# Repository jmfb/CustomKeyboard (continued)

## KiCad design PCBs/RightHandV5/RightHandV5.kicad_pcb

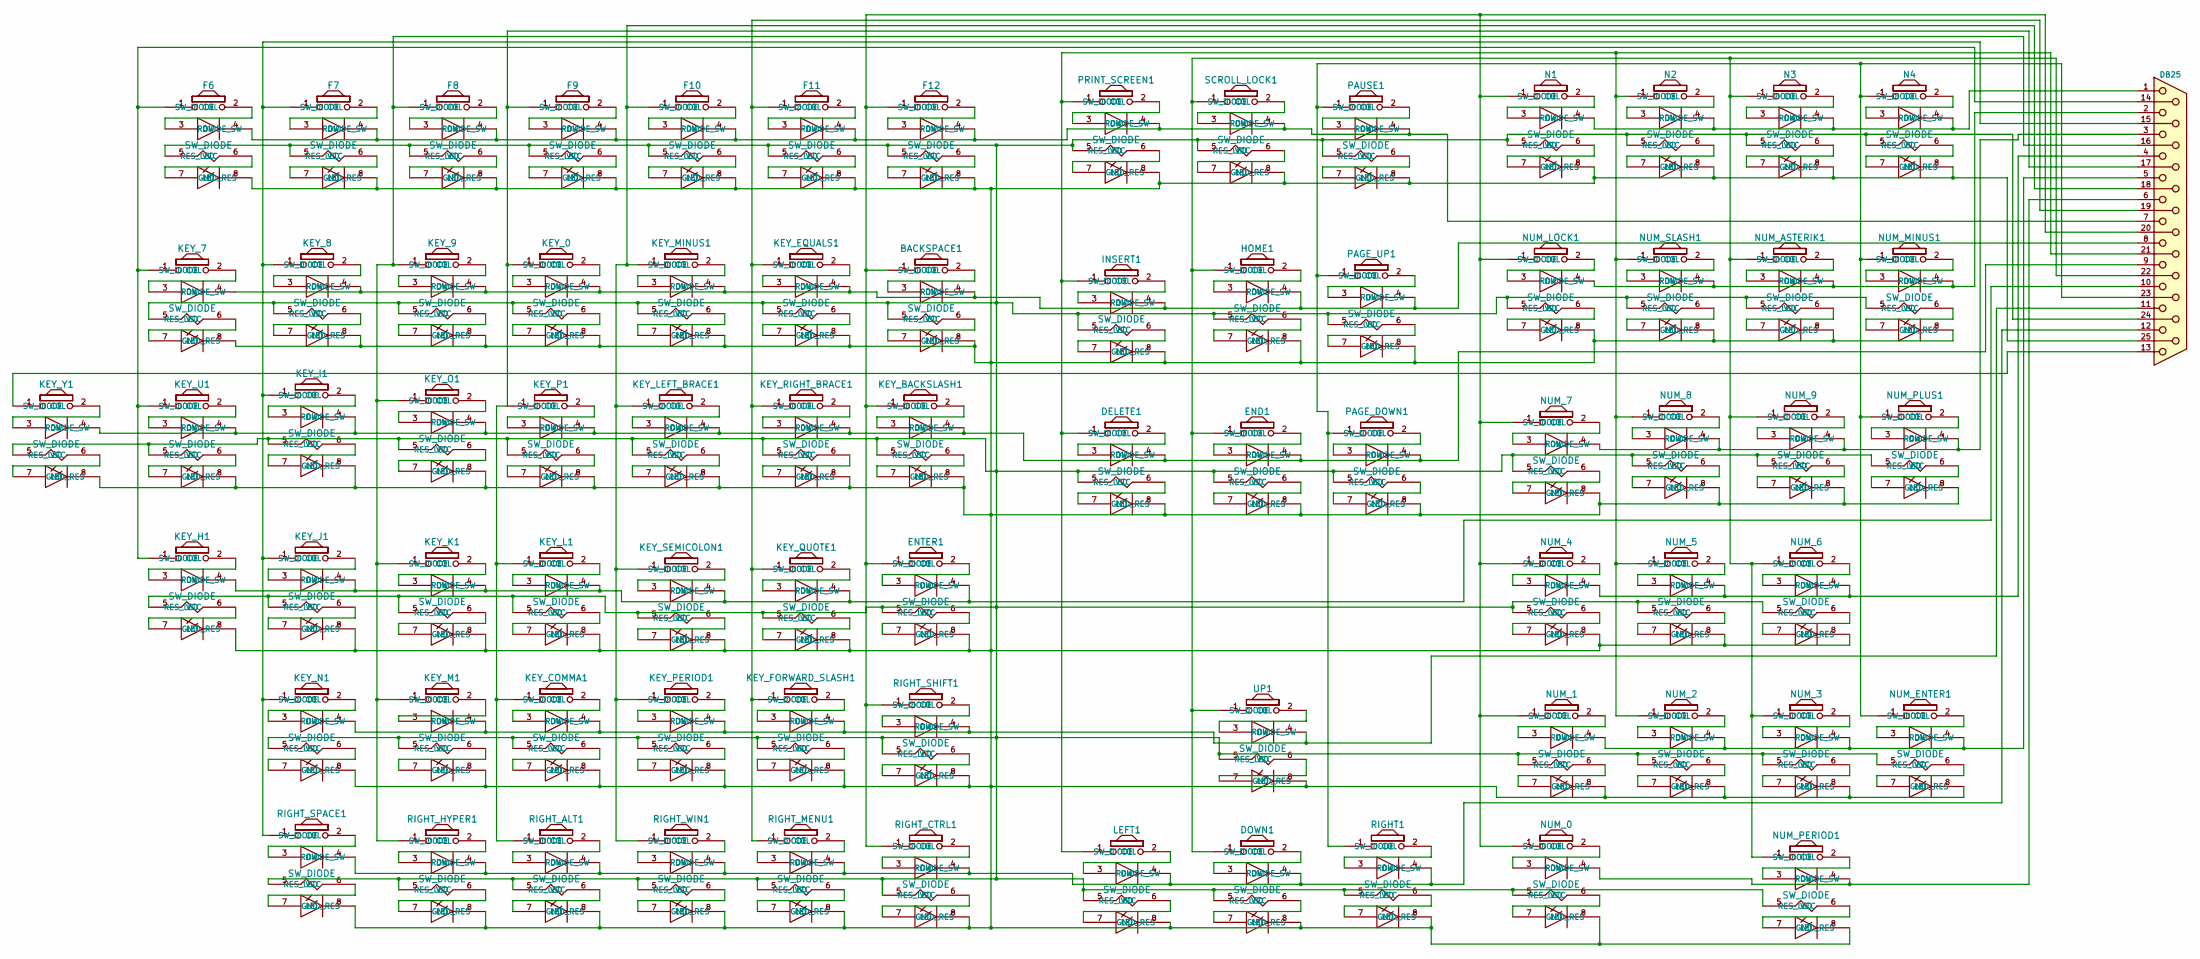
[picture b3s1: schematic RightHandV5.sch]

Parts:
BACKSPACE1: SW_DIODE; SW2_DIODE_R
DB25: DB25_Female; DB25FD
DELETE1: SW_DIODE
DOWN1: SW_DIODE
END1: SW_DIODE
ENTER1: SW_DIODE; SW2_DIODE_R
F6, F7, F8, F9, F10, F11, F12: SW_DIODE
HOME1: SW_DIODE
INSERT1: SW_DIODE
KEY_0, KEY_7, KEY_8, KEY_9: SW_DIODE
KEY_BACKSLASH1: SW_DIODE; SW_DIODE_RSIDE
KEY_COMMA1: SW_DIODE
KEY_EQUALS1: SW_DIODE
KEY_FORWARD_SLASH1: SW_DIODE
KEY_H1: SW_DIODE
KEY_I1: SW_DIODE
KEY_J1: SW_DIODE
KEY_K1: SW_DIODE
KEY_L1: SW_DIODE
KEY_LEFT_BRACE1: SW_DIODE
KEY_M1: SW_DIODE
KEY_MINUS1: SW_DIODE
KEY_N1: SW_DIODE
KEY_O1: SW_DIODE
KEY_P1: SW_DIODE
KEY_PERIOD1: SW_DIODE
KEY_QUOTE1: SW_DIODE
KEY_RIGHT_BRACE1: SW_DIODE; SW_DIODE_RTOP
KEY_SEMICOLON1: SW_DIODE
KEY_U1: SW_DIODE
KEY_Y1: SW_DIODE
LEFT1: SW_DIODE
N1, N2, N3, N4: SW_DIODE
NUM_0: SW_DIODE; SW2_DIODE_L
NUM_1, NUM_2, NUM_3, NUM_4, NUM_5, NUM_6, NUM_7, NUM_8, NUM_9: SW_DIODE
NUM_ASTERIK1: SW_DIODE
NUM_ENTER1: SW_DIODE; SW2_DIODE_L_RSIDE
NUM_LOCK1: SW_DIODE
NUM_MINUS1: SW_DIODE
NUM_PERIOD1: SW_DIODE
NUM_PLUS1: SW_DIODE; SW2_DIODE_L_RSIDE
NUM_SLASH1: SW_DIODE
PAGE_DOWN1: SW_DIODE
PAGE_UP1: SW_DIODE
PAUSE1: SW_DIODE
PRINT_SCREEN1: SW_DIODE
RIGHT1: SW_DIODE
RIGHT_ALT1: SW_DIODE
RIGHT_CTRL1: SW_DIODE; SW_DIODE_RTOP
RIGHT_HYPER1: SW_DIODE
RIGHT_MENU1: SW_DIODE; SW_DIODE_RTOP
RIGHT_SHIFT1: SW_DIODE; SW2_DIODE_R_RSIDE
RIGHT_SPACE1: SW_DIODE; SW2_DIODE_R_RSIDE
RIGHT_WIN1: SW_DIODE
SCROLL_LOCK1: SW_DIODE
UP1: SW_DIODE

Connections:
unnamed: BACKSPACE1.1 (COL), DB25.20, ENTER1.1 (COL), F12.1 (COL), KEY_BACKSLASH1.1 (COL), N1.1 (COL), NUM_0.1 (COL), NUM_1.1 (COL), NUM_4.1 (COL), NUM_7.1 (COL), NUM_LOCK1.1 (COL), RIGHT_CTRL1.1 (COL), RIGHT_SHIFT1.1 (COL)
unnamed: BACKSPACE1.2 (SW_DIODE), BACKSPACE1.3 (DIODE_SW)
unnamed: BACKSPACE1.4 (ROW), DB25.8, HOME1.4 (ROW), INSERT1.4 (ROW), KEY_0.4 (ROW), KEY_7.4 (ROW), KEY_8.4 (ROW), KEY_9.4 (ROW), KEY_EQUALS1.4 (ROW), KEY_MINUS1.4 (ROW), PAGE_UP1.4 (ROW)
unnamed: BACKSPACE1.5 (VCC), DB25.24, DELETE1.5 (VCC), DOWN1.5 (VCC), END1.5 (VCC), ENTER1.5 (VCC), F6.5 (VCC), F7.5 (VCC), F8.5 (VCC), F9.5 (VCC), F10.5 (VCC), F11.5 (VCC), F12.5 (VCC), HOME1.5 (VCC), INSERT1.5 (VCC), KEY_0.5 (VCC), KEY_7.5 (VCC), KEY_8.5 (VCC), KEY_9.5 (VCC), KEY_BACKSLASH1.5 (VCC), KEY_COMMA1.5 (VCC), KEY_EQUALS1.5 (VCC), KEY_FORWARD_SLASH1.5 (VCC), KEY_H1.5 (VCC), KEY_I1.5 (VCC), KEY_J1.5 (VCC), KEY_K1.5 (VCC), KEY_L1.5 (VCC), KEY_LEFT_BRACE1.5 (VCC), KEY_M1.5 (VCC), KEY_MINUS1.5 (VCC), KEY_N1.5 (VCC), KEY_O1.5 (VCC), KEY_P1.5 (VCC), KEY_PERIOD1.5 (VCC), KEY_QUOTE1.5 (VCC), KEY_RIGHT_BRACE1.5 (VCC), KEY_SEMICOLON1.5 (VCC), KEY_U1.5 (VCC), KEY_Y1.5 (VCC), LEFT1.5 (VCC), N1.5 (VCC), N2.5 (VCC), N3.5 (VCC), N4.5 (VCC), NUM_0.5 (VCC), NUM_1.5 (VCC), NUM_2.5 (VCC), NUM_3.5 (VCC), NUM_4.5 (VCC), NUM_5.5 (VCC), NUM_6.5 (VCC), NUM_7.5 (VCC), NUM_8.5 (VCC), NUM_9.5 (VCC), NUM_ASTERIK1.5 (VCC), NUM_ENTER1.5 (VCC), NUM_LOCK1.5 (VCC), NUM_MINUS1.5 (VCC), NUM_PERIOD1.5 (VCC), NUM_PLUS1.5 (VCC), NUM_SLASH1.5 (VCC), PAGE_DOWN1.5 (VCC), PAGE_UP1.5 (VCC), PAUSE1.5 (VCC), PRINT_SCREEN1.5 (VCC), RIGHT1.5 (VCC), RIGHT_ALT1.5 (VCC), RIGHT_CTRL1.5 (VCC), RIGHT_HYPER1.5 (VCC), RIGHT_MENU1.5 (VCC), RIGHT_SHIFT1.5 (VCC), RIGHT_SPACE1.5 (VCC), RIGHT_WIN1.5 (VCC), SCROLL_LOCK1.5 (VCC), UP1.5 (VCC)
unnamed: BACKSPACE1.6 (RES_LED), BACKSPACE1.7 (LED_RES)
unnamed: BACKSPACE1.8 (GND), DB25.25, DELETE1.8 (GND), DOWN1.8 (GND), END1.8 (GND), ENTER1.8 (GND), F6.8 (GND), F7.8 (GND), F8.8 (GND), F9.8 (GND), F10.8 (GND), F11.8 (GND), F12.8 (GND), HOME1.8 (GND), INSERT1.8 (GND), KEY_0.8 (GND), KEY_7.8 (GND), KEY_8.8 (GND), KEY_9.8 (GND), KEY_BACKSLASH1.8 (GND), KEY_COMMA1.8 (GND), KEY_EQUALS1.8 (GND), KEY_FORWARD_SLASH1.8 (GND), KEY_H1.8 (GND), KEY_I1.8 (GND), KEY_J1.8 (GND), KEY_K1.8 (GND), KEY_L1.8 (GND), KEY_LEFT_BRACE1.8 (GND), KEY_M1.8 (GND), KEY_MINUS1.8 (GND), KEY_N1.8 (GND), KEY_O1.8 (GND), KEY_P1.8 (GND), KEY_PERIOD1.8 (GND), KEY_QUOTE1.8 (GND), KEY_RIGHT_BRACE1.8 (GND), KEY_SEMICOLON1.8 (GND), KEY_U1.8 (GND), KEY_Y1.8 (GND), LEFT1.8 (GND), N1.8 (GND), N2.8 (GND), N3.8 (GND), N4.8 (GND), NUM_0.8 (GND), NUM_1.8 (GND), NUM_2.8 (GND), NUM_3.8 (GND), NUM_4.8 (GND), NUM_5.8 (GND), NUM_6.8 (GND), NUM_7.8 (GND), NUM_8.8 (GND), NUM_9.8 (GND), NUM_ASTERIK1.8 (GND), NUM_ENTER1.8 (GND), NUM_LOCK1.8 (GND), NUM_MINUS1.8 (GND), NUM_PERIOD1.8 (GND), NUM_PLUS1.8 (GND), NUM_SLASH1.8 (GND), PAGE_DOWN1.8 (GND), PAGE_UP1.8 (GND), PAUSE1.8 (GND), PRINT_SCREEN1.8 (GND), RIGHT1.8 (GND), RIGHT_ALT1.8 (GND), RIGHT_CTRL1.8 (GND), RIGHT_HYPER1.8 (GND), RIGHT_MENU1.8 (GND), RIGHT_SHIFT1.8 (GND), RIGHT_SPACE1.8 (GND), RIGHT_WIN1.8 (GND), SCROLL_LOCK1.8 (GND), UP1.8 (GND)
unnamed: DB25.1, N1.4 (ROW), N2.4 (ROW), N3.4 (ROW), N4.4 (ROW)
unnamed: DB25.2, NUM_ASTERIK1.4 (ROW), NUM_LOCK1.4 (ROW), NUM_MINUS1.4 (ROW), NUM_SLASH1.4 (ROW)
unnamed: DB25.3, NUM_7.4 (ROW), NUM_8.4 (ROW), NUM_9.4 (ROW), NUM_PLUS1.4 (ROW)
unnamed: DB25.4, NUM_4.4 (ROW), NUM_5.4 (ROW), NUM_6.4 (ROW)
unnamed: DB25.5, NUM_1.4 (ROW), NUM_2.4 (ROW), NUM_3.4 (ROW), NUM_ENTER1.4 (ROW)
unnamed: DB25.6, NUM_0.4 (ROW), NUM_PERIOD1.4 (ROW)
unnamed: DB25.7, F6.4 (ROW), F7.4 (ROW), F8.4 (ROW), F9.4 (ROW), F10.4 (ROW), F11.4 (ROW), F12.4 (ROW), PAUSE1.4 (ROW), PRINT_SCREEN1.4 (ROW), SCROLL_LOCK1.4 (ROW)
unnamed: DB25.9, DELETE1.4 (ROW), END1.4 (ROW), KEY_BACKSLASH1.4 (ROW), KEY_I1.4 (ROW), KEY_LEFT_BRACE1.4 (ROW), KEY_O1.4 (ROW), KEY_P1.4 (ROW), KEY_RIGHT_BRACE1.4 (ROW), KEY_U1.4 (ROW), KEY_Y1.4 (ROW), PAGE_DOWN1.4 (ROW)
unnamed: DB25.10, ENTER1.4 (ROW), KEY_H1.4 (ROW), KEY_J1.4 (ROW), KEY_K1.4 (ROW), KEY_L1.4 (ROW), KEY_QUOTE1.4 (ROW), KEY_SEMICOLON1.4 (ROW)
unnamed: DB25.11, KEY_COMMA1.4 (ROW), KEY_FORWARD_SLASH1.4 (ROW), KEY_M1.4 (ROW), KEY_N1.4 (ROW), KEY_PERIOD1.4 (ROW), RIGHT_SHIFT1.4 (ROW), UP1.4 (ROW)
unnamed: DB25.12, DOWN1.4 (ROW), LEFT1.4 (ROW), RIGHT1.4 (ROW), RIGHT_ALT1.4 (ROW), RIGHT_CTRL1.4 (ROW), RIGHT_HYPER1.4 (ROW), RIGHT_MENU1.4 (ROW), RIGHT_SPACE1.4 (ROW), RIGHT_WIN1.4 (ROW)
unnamed: DB25.13, KEY_Y1.1 (COL)
unnamed: DB25.14, F6.1 (COL), KEY_7.1 (COL), KEY_H1.1 (COL), KEY_U1.1 (COL)
unnamed: DB25.15, F7.1 (COL), KEY_8.1 (COL), KEY_I1.1 (COL), KEY_J1.1 (COL), KEY_N1.1 (COL), RIGHT_SPACE1.1 (COL)
unnamed: DB25.16, F8.1 (COL), KEY_9.1 (COL), KEY_K1.1 (COL), KEY_M1.1 (COL), KEY_O1.1 (COL), RIGHT_HYPER1.1 (COL)
unnamed: DB25.17, F9.1 (COL), KEY_0.1 (COL), KEY_COMMA1.1 (COL), KEY_L1.1 (COL), KEY_P1.1 (COL), RIGHT_ALT1.1 (COL)
unnamed: DB25.18, F10.1 (COL), KEY_LEFT_BRACE1.1 (COL), KEY_MINUS1.1 (COL), KEY_PERIOD1.1 (COL), KEY_SEMICOLON1.1 (COL), RIGHT_WIN1.1 (COL)
unnamed: DB25.19, F11.1 (COL), KEY_EQUALS1.1 (COL), KEY_FORWARD_SLASH1.1 (COL), KEY_QUOTE1.1 (COL), KEY_RIGHT_BRACE1.1 (COL), RIGHT_MENU1.1 (COL)
unnamed: DB25.21, DELETE1.1 (COL), INSERT1.1 (COL), LEFT1.1 (COL), N2.1 (COL), NUM_2.1 (COL), NUM_5.1 (COL), NUM_8.1 (COL), NUM_SLASH1.1 (COL), PRINT_SCREEN1.1 (COL)
unnamed: DB25.22, DOWN1.1 (COL), END1.1 (COL), HOME1.1 (COL), N3.1 (COL), NUM_3.1 (COL), NUM_6.1 (COL), NUM_9.1 (COL), NUM_ASTERIK1.1 (COL), NUM_PERIOD1.1 (COL), SCROLL_LOCK1.1 (COL), UP1.1 (COL)
unnamed: DB25.23, N4.1 (COL), NUM_ENTER1.1 (COL), NUM_MINUS1.1 (COL), NUM_PLUS1.1 (COL), PAGE_DOWN1.1 (COL), PAGE_UP1.1 (COL), PAUSE1.1 (COL), RIGHT1.1 (COL)
unnamed: DELETE1.2 (SW_DIODE), DELETE1.3 (DIODE_SW)
unnamed: DELETE1.6 (RES_LED), DELETE1.7 (LED_RES)
unnamed: DOWN1.2 (SW_DIODE), DOWN1.3 (DIODE_SW)
unnamed: DOWN1.6 (RES_LED), DOWN1.7 (LED_RES)
unnamed: END1.2 (SW_DIODE), END1.3 (DIODE_SW)
unnamed: END1.6 (RES_LED), END1.7 (LED_RES)
unnamed: ENTER1.2 (SW_DIODE), ENTER1.3 (DIODE_SW)
unnamed: ENTER1.6 (RES_LED), ENTER1.7 (LED_RES)
unnamed: F6.2 (SW_DIODE), F6.3 (DIODE_SW)
unnamed: F6.6 (RES_LED), F6.7 (LED_RES)
unnamed: F7.2 (SW_DIODE), F7.3 (DIODE_SW)
unnamed: F7.6 (RES_LED), F7.7 (LED_RES)
unnamed: F8.2 (SW_DIODE), F8.3 (DIODE_SW)
unnamed: F8.6 (RES_LED), F8.7 (LED_RES)
unnamed: F9.2 (SW_DIODE), F9.3 (DIODE_SW)
unnamed: F9.6 (RES_LED), F9.7 (LED_RES)
unnamed: F10.2 (SW_DIODE), F10.3 (DIODE_SW)
unnamed: F10.6 (RES_LED), F10.7 (LED_RES)
unnamed: F11.2 (SW_DIODE), F11.3 (DIODE_SW)
unnamed: F11.6 (RES_LED), F11.7 (LED_RES)
unnamed: F12.2 (SW_DIODE), F12.3 (DIODE_SW)
unnamed: F12.6 (RES_LED), F12.7 (LED_RES)
unnamed: HOME1.2 (SW_DIODE), HOME1.3 (DIODE_SW)
unnamed: HOME1.6 (RES_LED), HOME1.7 (LED_RES)
unnamed: INSERT1.2 (SW_DIODE), INSERT1.3 (DIODE_SW)
unnamed: INSERT1.6 (RES_LED), INSERT1.7 (LED_RES)
unnamed: KEY_0.2 (SW_DIODE), KEY_0.3 (DIODE_SW)
unnamed: KEY_0.6 (RES_LED), KEY_0.7 (LED_RES)
unnamed: KEY_7.2 (SW_DIODE), KEY_7.3 (DIODE_SW)
unnamed: KEY_7.6 (RES_LED), KEY_7.7 (LED_RES)
unnamed: KEY_8.2 (SW_DIODE), KEY_8.3 (DIODE_SW)
unnamed: KEY_8.6 (RES_LED), KEY_8.7 (LED_RES)
unnamed: KEY_9.2 (SW_DIODE), KEY_9.3 (DIODE_SW)
unnamed: KEY_9.6 (RES_LED), KEY_9.7 (LED_RES)
unnamed: KEY_BACKSLASH1.2 (SW_DIODE), KEY_BACKSLASH1.3 (DIODE_SW)
unnamed: KEY_BACKSLASH1.6 (RES_LED), KEY_BACKSLASH1.7 (LED_RES)
unnamed: KEY_COMMA1.2 (SW_DIODE), KEY_COMMA1.3 (DIODE_SW)
unnamed: KEY_COMMA1.6 (RES_LED), KEY_COMMA1.7 (LED_RES)
unnamed: KEY_EQUALS1.2 (SW_DIODE), KEY_EQUALS1.3 (DIODE_SW)
unnamed: KEY_EQUALS1.6 (RES_LED), KEY_EQUALS1.7 (LED_RES)
unnamed: KEY_FORWARD_SLASH1.2 (SW_DIODE), KEY_FORWARD_SLASH1.3 (DIODE_SW)
unnamed: KEY_FORWARD_SLASH1.6 (RES_LED), KEY_FORWARD_SLASH1.7 (LED_RES)
unnamed: KEY_H1.2 (SW_DIODE), KEY_H1.3 (DIODE_SW)
unnamed: KEY_H1.6 (RES_LED), KEY_H1.7 (LED_RES)
unnamed: KEY_I1.2 (SW_DIODE), KEY_I1.3 (DIODE_SW)
unnamed: KEY_I1.6 (RES_LED), KEY_I1.7 (LED_RES)
unnamed: KEY_J1.2 (SW_DIODE), KEY_J1.3 (DIODE_SW)
unnamed: KEY_J1.6 (RES_LED), KEY_J1.7 (LED_RES)
unnamed: KEY_K1.2 (SW_DIODE), KEY_K1.3 (DIODE_SW)
unnamed: KEY_K1.6 (RES_LED), KEY_K1.7 (LED_RES)
unnamed: KEY_L1.2 (SW_DIODE), KEY_L1.3 (DIODE_SW)
unnamed: KEY_L1.6 (RES_LED), KEY_L1.7 (LED_RES)
unnamed: KEY_LEFT_BRACE1.2 (SW_DIODE), KEY_LEFT_BRACE1.3 (DIODE_SW)
unnamed: KEY_LEFT_BRACE1.6 (RES_LED), KEY_LEFT_BRACE1.7 (LED_RES)
unnamed: KEY_M1.2 (SW_DIODE), KEY_M1.3 (DIODE_SW)
unnamed: KEY_M1.6 (RES_LED), KEY_M1.7 (LED_RES)
unnamed: KEY_MINUS1.2 (SW_DIODE), KEY_MINUS1.3 (DIODE_SW)
unnamed: KEY_MINUS1.6 (RES_LED), KEY_MINUS1.7 (LED_RES)
unnamed: KEY_N1.2 (SW_DIODE), KEY_N1.3 (DIODE_SW)
unnamed: KEY_N1.6 (RES_LED), KEY_N1.7 (LED_RES)
unnamed: KEY_O1.2 (SW_DIODE), KEY_O1.3 (DIODE_SW)
unnamed: KEY_O1.6 (RES_LED), KEY_O1.7 (LED_RES)
unnamed: KEY_P1.2 (SW_DIODE), KEY_P1.3 (DIODE_SW)
unnamed: KEY_P1.6 (RES_LED), KEY_P1.7 (LED_RES)
unnamed: KEY_PERIOD1.2 (SW_DIODE), KEY_PERIOD1.3 (DIODE_SW)
unnamed: KEY_PERIOD1.6 (RES_LED), KEY_PERIOD1.7 (LED_RES)
unnamed: KEY_QUOTE1.2 (SW_DIODE), KEY_QUOTE1.3 (DIODE_SW)
unnamed: KEY_QUOTE1.6 (RES_LED), KEY_QUOTE1.7 (LED_RES)
unnamed: KEY_RIGHT_BRACE1.2 (SW_DIODE), KEY_RIGHT_BRACE1.3 (DIODE_SW)
unnamed: KEY_RIGHT_BRACE1.6 (RES_LED), KEY_RIGHT_BRACE1.7 (LED_RES)
unnamed: KEY_SEMICOLON1.2 (SW_DIODE), KEY_SEMICOLON1.3 (DIODE_SW)
unnamed: KEY_SEMICOLON1.6 (RES_LED), KEY_SEMICOLON1.7 (LED_RES)
unnamed: KEY_U1.2 (SW_DIODE), KEY_U1.3 (DIODE_SW)
unnamed: KEY_U1.6 (RES_LED), KEY_U1.7 (LED_RES)
unnamed: KEY_Y1.2 (SW_DIODE), KEY_Y1.3 (DIODE_SW)
unnamed: KEY_Y1.6 (RES_LED), KEY_Y1.7 (LED_RES)
unnamed: LEFT1.2 (SW_DIODE), LEFT1.3 (DIODE_SW)
unnamed: LEFT1.6 (RES_LED), LEFT1.7 (LED_RES)
unnamed: N1.2 (SW_DIODE), N1.3 (DIODE_SW)
unnamed: N1.6 (RES_LED), N1.7 (LED_RES)
unnamed: N2.2 (SW_DIODE), N2.3 (DIODE_SW)
unnamed: N2.6 (RES_LED), N2.7 (LED_RES)
unnamed: N3.2 (SW_DIODE), N3.3 (DIODE_SW)
unnamed: N3.6 (RES_LED), N3.7 (LED_RES)
unnamed: N4.2 (SW_DIODE), N4.3 (DIODE_SW)
unnamed: N4.6 (RES_LED), N4.7 (LED_RES)
unnamed: NUM_0.2 (SW_DIODE), NUM_0.3 (DIODE_SW)
unnamed: NUM_0.6 (RES_LED), NUM_0.7 (LED_RES)
unnamed: NUM_1.2 (SW_DIODE), NUM_1.3 (DIODE_SW)
unnamed: NUM_1.6 (RES_LED), NUM_1.7 (LED_RES)
unnamed: NUM_2.2 (SW_DIODE), NUM_2.3 (DIODE_SW)
unnamed: NUM_2.6 (RES_LED), NUM_2.7 (LED_RES)
unnamed: NUM_3.2 (SW_DIODE), NUM_3.3 (DIODE_SW)
unnamed: NUM_3.6 (RES_LED), NUM_3.7 (LED_RES)
unnamed: NUM_4.2 (SW_DIODE), NUM_4.3 (DIODE_SW)
unnamed: NUM_4.6 (RES_LED), NUM_4.7 (LED_RES)
unnamed: NUM_5.2 (SW_DIODE), NUM_5.3 (DIODE_SW)
unnamed: NUM_5.6 (RES_LED), NUM_5.7 (LED_RES)
unnamed: NUM_6.2 (SW_DIODE), NUM_6.3 (DIODE_SW)
unnamed: NUM_6.6 (RES_LED), NUM_6.7 (LED_RES)
unnamed: NUM_7.2 (SW_DIODE), NUM_7.3 (DIODE_SW)
unnamed: NUM_7.6 (RES_LED), NUM_7.7 (LED_RES)
unnamed: NUM_8.2 (SW_DIODE), NUM_8.3 (DIODE_SW)
unnamed: NUM_8.6 (RES_LED), NUM_8.7 (LED_RES)
unnamed: NUM_9.2 (SW_DIODE), NUM_9.3 (DIODE_SW)
unnamed: NUM_9.6 (RES_LED), NUM_9.7 (LED_RES)
unnamed: NUM_ASTERIK1.2 (SW_DIODE), NUM_ASTERIK1.3 (DIODE_SW)
unnamed: NUM_ASTERIK1.6 (RES_LED), NUM_ASTERIK1.7 (LED_RES)
unnamed: NUM_ENTER1.2 (SW_DIODE), NUM_ENTER1.3 (DIODE_SW)
unnamed: NUM_ENTER1.6 (RES_LED), NUM_ENTER1.7 (LED_RES)
unnamed: NUM_LOCK1.2 (SW_DIODE), NUM_LOCK1.3 (DIODE_SW)
unnamed: NUM_LOCK1.6 (RES_LED), NUM_LOCK1.7 (LED_RES)
unnamed: NUM_MINUS1.2 (SW_DIODE), NUM_MINUS1.3 (DIODE_SW)
unnamed: NUM_MINUS1.6 (RES_LED), NUM_MINUS1.7 (LED_RES)
unnamed: NUM_PERIOD1.2 (SW_DIODE), NUM_PERIOD1.3 (DIODE_SW)
unnamed: NUM_PERIOD1.6 (RES_LED), NUM_PERIOD1.7 (LED_RES)
unnamed: NUM_PLUS1.2 (SW_DIODE), NUM_PLUS1.3 (DIODE_SW)
unnamed: NUM_PLUS1.6 (RES_LED), NUM_PLUS1.7 (LED_RES)
unnamed: NUM_SLASH1.2 (SW_DIODE), NUM_SLASH1.3 (DIODE_SW)
unnamed: NUM_SLASH1.6 (RES_LED), NUM_SLASH1.7 (LED_RES)
unnamed: PAGE_DOWN1.2 (SW_DIODE), PAGE_DOWN1.3 (DIODE_SW)
unnamed: PAGE_DOWN1.6 (RES_LED), PAGE_DOWN1.7 (LED_RES)
unnamed: PAGE_UP1.2 (SW_DIODE), PAGE_UP1.3 (DIODE_SW)
unnamed: PAGE_UP1.6 (RES_LED), PAGE_UP1.7 (LED_RES)
unnamed: PAUSE1.2 (SW_DIODE), PAUSE1.3 (DIODE_SW)
unnamed: PAUSE1.6 (RES_LED), PAUSE1.7 (LED_RES)
unnamed: PRINT_SCREEN1.2 (SW_DIODE), PRINT_SCREEN1.3 (DIODE_SW)
unnamed: PRINT_SCREEN1.6 (RES_LED), PRINT_SCREEN1.7 (LED_RES)
unnamed: RIGHT1.2 (SW_DIODE), RIGHT1.3 (DIODE_SW)
unnamed: RIGHT1.6 (RES_LED), RIGHT1.7 (LED_RES)
unnamed: RIGHT_ALT1.2 (SW_DIODE), RIGHT_ALT1.3 (DIODE_SW)
unnamed: RIGHT_ALT1.6 (RES_LED), RIGHT_ALT1.7 (LED_RES)
unnamed: RIGHT_CTRL1.2 (SW_DIODE), RIGHT_CTRL1.3 (DIODE_SW)
unnamed: RIGHT_CTRL1.6 (RES_LED), RIGHT_CTRL1.7 (LED_RES)
unnamed: RIGHT_HYPER1.2 (SW_DIODE), RIGHT_HYPER1.3 (DIODE_SW)
unnamed: RIGHT_HYPER1.6 (RES_LED), RIGHT_HYPER1.7 (LED_RES)
unnamed: RIGHT_MENU1.2 (SW_DIODE), RIGHT_MENU1.3 (DIODE_SW)
unnamed: RIGHT_MENU1.6 (RES_LED), RIGHT_MENU1.7 (LED_RES)
unnamed: RIGHT_SHIFT1.2 (SW_DIODE), RIGHT_SHIFT1.3 (DIODE_SW)
unnamed: RIGHT_SHIFT1.6 (RES_LED), RIGHT_SHIFT1.7 (LED_RES)
unnamed: RIGHT_SPACE1.2 (SW_DIODE), RIGHT_SPACE1.3 (DIODE_SW)
unnamed: RIGHT_SPACE1.6 (RES_LED), RIGHT_SPACE1.7 (LED_RES)
unnamed: RIGHT_WIN1.2 (SW_DIODE), RIGHT_WIN1.3 (DIODE_SW)
unnamed: RIGHT_WIN1.6 (RES_LED), RIGHT_WIN1.7 (LED_RES)
unnamed: SCROLL_LOCK1.2 (SW_DIODE), SCROLL_LOCK1.3 (DIODE_SW)
unnamed: SCROLL_LOCK1.6 (RES_LED), SCROLL_LOCK1.7 (LED_RES)
unnamed: UP1.2 (SW_DIODE), UP1.3 (DIODE_SW)
unnamed: UP1.6 (RES_LED), UP1.7 (LED_RES)

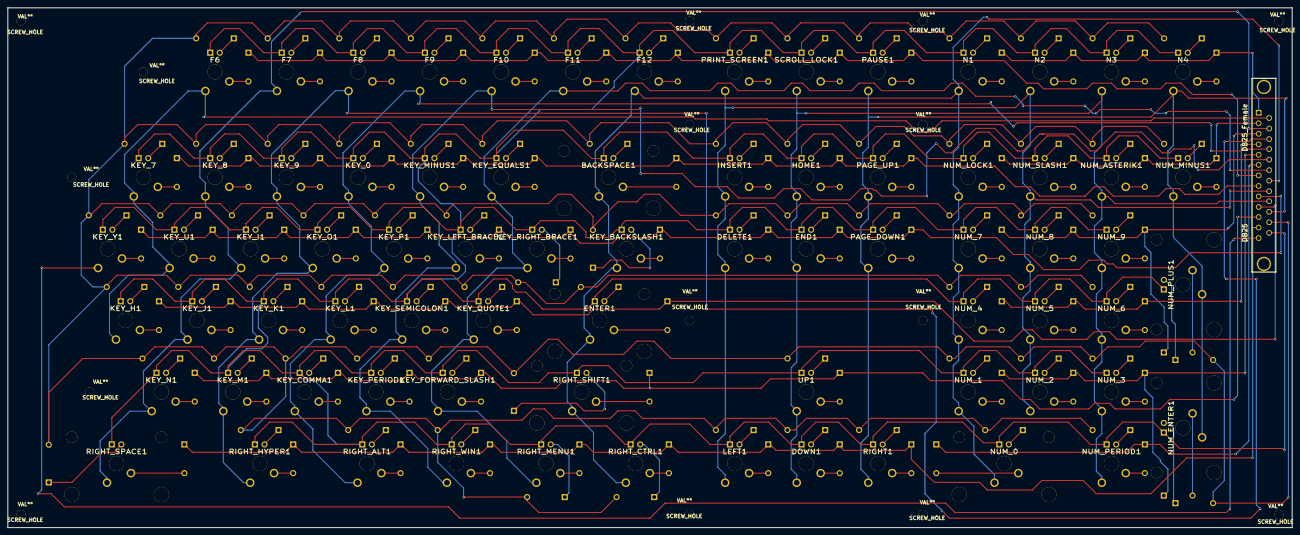
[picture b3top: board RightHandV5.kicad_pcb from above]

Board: 2 copper layers, 341.0 x 138.0 mm, 91 parts (0 on the bottom side), 175 nets.

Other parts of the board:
SCREW_HOLE: VAL**; SCREW_HOLE
SCREW_HOLE#2, SCREW_HOLE#3, SCREW_HOLE#4, SCREW_HOLE#5, SCREW_HOLE#6, SCREW_HOLE#7, SCREW_HOLE#8, SCREW_HOLE#9, SCREW_HOLE#10, SCREW_HOLE#11, SCREW_HOLE#12, SCREW_HOLE#13, SCREW_HOLE#14, SCREW_HOLE#15: VAL**; SCREW_HOLE

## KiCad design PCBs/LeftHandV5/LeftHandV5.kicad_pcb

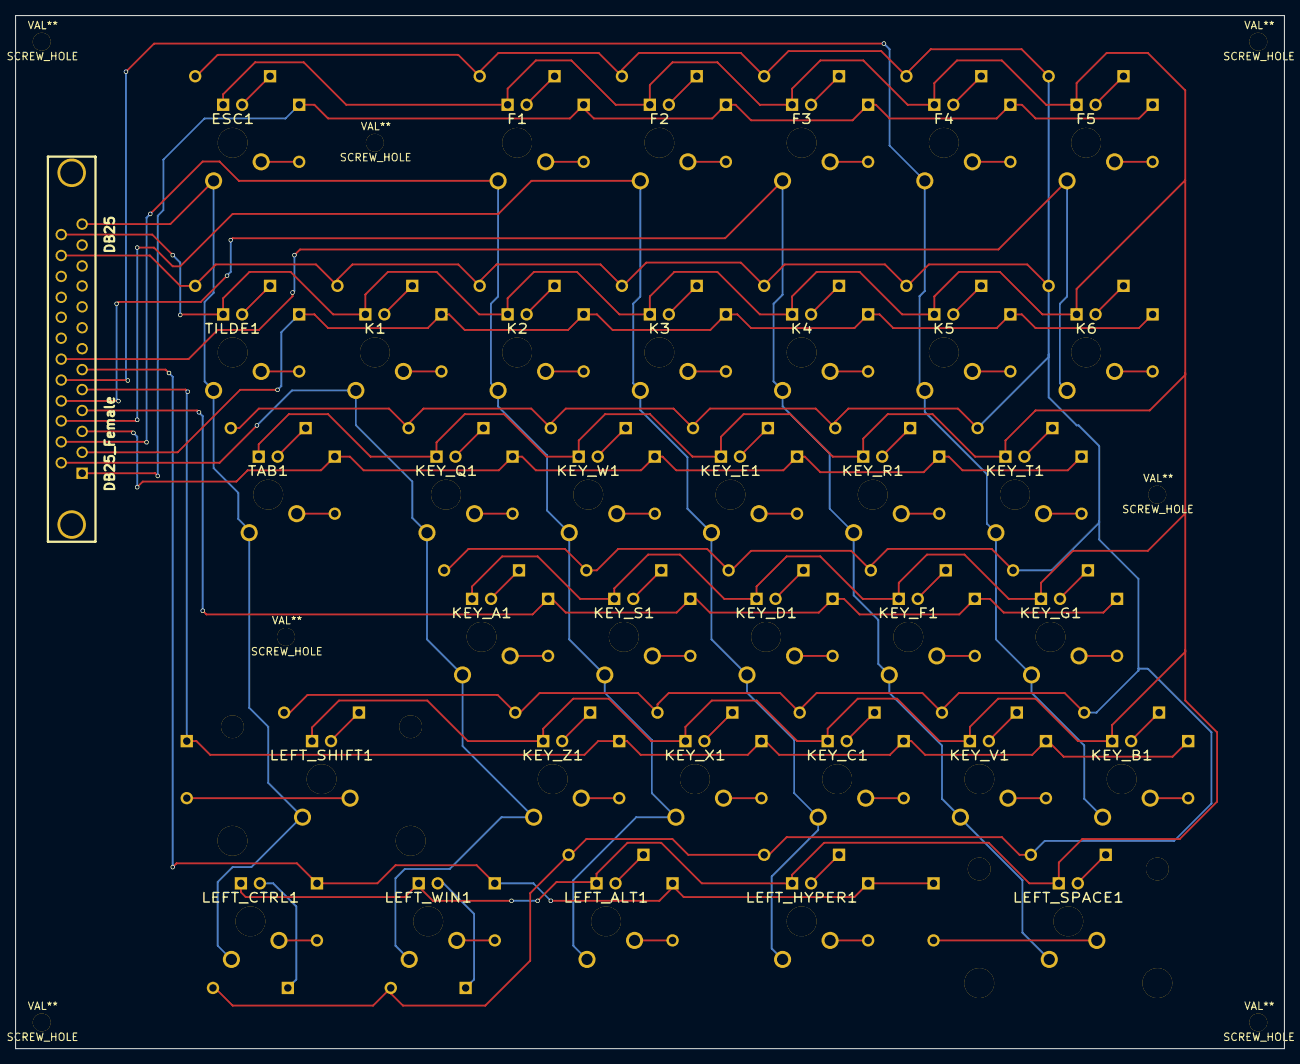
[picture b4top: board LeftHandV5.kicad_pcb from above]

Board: 2 copper layers, 169.5 x 138.0 mm, 43 parts (0 on the bottom side), 85 nets.

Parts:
DB25: DB25_Female; DB25FD
ESC1: SW_DIODE
F1, F2, F3, F4, F5: SW_DIODE
K1, K2, K3, K4, K5, K6: SW_DIODE
KEY_A1: SW_DIODE
KEY_B1: SW_DIODE
KEY_C1: SW_DIODE
KEY_D1: SW_DIODE
KEY_E1: SW_DIODE
KEY_F1: SW_DIODE
KEY_G1: SW_DIODE
KEY_Q1: SW_DIODE
KEY_R1: SW_DIODE
KEY_S1: SW_DIODE
KEY_T1: SW_DIODE
KEY_V1: SW_DIODE
KEY_W1: SW_DIODE
KEY_X1: SW_DIODE
KEY_Z1: SW_DIODE
LEFT_ALT1: SW_DIODE
LEFT_CTRL1: SW_DIODE; SW_DIODE_RTOP
LEFT_HYPER1: SW_DIODE
LEFT_SHIFT1: SW_DIODE; SW2_DIODE_L
LEFT_SPACE1: SW_DIODE; SW2_DIODE_L
LEFT_WIN1: SW_DIODE; SW_DIODE_RTOP
SCREW_HOLE: VAL**; SCREW_HOLE
SCREW_HOLE#2, SCREW_HOLE#3, SCREW_HOLE#4, SCREW_HOLE#5, SCREW_HOLE#6, SCREW_HOLE#7: VAL**; SCREW_HOLE
TAB1: SW_DIODE
TILDE1: SW_DIODE

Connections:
unnamed: DB25.1, ESC1.4, F1.4, F2.4, F3.4, F4.4, F5.4
unnamed: DB25.2, K1.4, K2.4, K3.4, K4.4, K5.4, K6.4, TILDE1.4
unnamed: DB25.3, KEY_E1.4, KEY_Q1.4, KEY_R1.4, KEY_T1.4, KEY_W1.4, TAB1.4
unnamed: DB25.4, KEY_A1.4, KEY_D1.4, KEY_F1.4, KEY_G1.4, KEY_S1.4
unnamed: DB25.5, KEY_B1.4, KEY_C1.4, KEY_V1.4, KEY_X1.4, KEY_Z1.4, LEFT_SHIFT1.4
unnamed: DB25.6, LEFT_ALT1.4, LEFT_CTRL1.4, LEFT_HYPER1.4, LEFT_SPACE1.4, LEFT_WIN1.4
unnamed: DB25.13, ESC1.1, LEFT_CTRL1.1, LEFT_SHIFT1.1, TAB1.1, TILDE1.1
unnamed: DB25.14, K1.1, KEY_A1.1, KEY_Q1.1, KEY_Z1.1, LEFT_WIN1.1
unnamed: DB25.15, F1.1, K2.1, KEY_S1.1, KEY_W1.1, KEY_X1.1, LEFT_ALT1.1
unnamed: DB25.16, F2.1, K3.1, KEY_C1.1, KEY_D1.1, KEY_E1.1, LEFT_HYPER1.1
unnamed: DB25.17, F3.1, K4.1, KEY_F1.1, KEY_R1.1, KEY_V1.1, LEFT_SPACE1.1
unnamed: DB25.18, F4.1, K5.1, KEY_B1.1, KEY_G1.1, KEY_T1.1
unnamed: DB25.19, F5.1, K6.1
unnamed: DB25.24, ESC1.5, F1.5, F2.5, F3.5, F4.5, F5.5, K1.5, K2.5, K3.5, K4.5, K5.5, K6.5, KEY_A1.5, KEY_B1.5, KEY_C1.5, KEY_D1.5, KEY_E1.5, KEY_F1.5, KEY_G1.5, KEY_Q1.5, KEY_R1.5, KEY_S1.5, KEY_T1.5, KEY_V1.5, KEY_W1.5, KEY_X1.5, KEY_Z1.5, LEFT_ALT1.5, LEFT_CTRL1.5, LEFT_HYPER1.5, LEFT_SHIFT1.5, LEFT_SPACE1.5, LEFT_WIN1.5, TAB1.5, TILDE1.5
unnamed: DB25.25, ESC1.8, F1.8, F2.8, F3.8, F4.8, F5.8, K1.8, K2.8, K3.8, K4.8, K5.8, K6.8, KEY_A1.8, KEY_B1.8, KEY_C1.8, KEY_D1.8, KEY_E1.8, KEY_F1.8, KEY_G1.8, KEY_Q1.8, KEY_R1.8, KEY_S1.8, KEY_T1.8, KEY_V1.8, KEY_W1.8, KEY_X1.8, KEY_Z1.8, LEFT_ALT1.8, LEFT_CTRL1.8, LEFT_HYPER1.8, LEFT_SHIFT1.8, LEFT_SPACE1.8, LEFT_WIN1.8, TAB1.8, TILDE1.8
unnamed: ESC1.2, ESC1.3
unnamed: ESC1.6, ESC1.7
unnamed: F1.2, F1.3
unnamed: F1.6, F1.7
unnamed: F2.2, F2.3
unnamed: F2.6, F2.7
unnamed: F3.2, F3.3
unnamed: F3.6, F3.7
unnamed: F4.2, F4.3
unnamed: F4.6, F4.7
unnamed: F5.2, F5.3
unnamed: F5.6, F5.7
unnamed: K1.2, K1.3
unnamed: K1.6, K1.7
unnamed: K2.2, K2.3
unnamed: K2.6, K2.7
unnamed: K3.2, K3.3
unnamed: K3.6, K3.7
unnamed: K4.2, K4.3
unnamed: K4.6, K4.7
unnamed: K5.2, K5.3
unnamed: K5.6, K5.7
unnamed: K6.2, K6.3
unnamed: K6.6, K6.7
unnamed: KEY_A1.2, KEY_A1.3
unnamed: KEY_A1.6, KEY_A1.7
unnamed: KEY_B1.2, KEY_B1.3
unnamed: KEY_B1.6, KEY_B1.7
unnamed: KEY_C1.2, KEY_C1.3
unnamed: KEY_C1.6, KEY_C1.7
unnamed: KEY_D1.2, KEY_D1.3
unnamed: KEY_D1.6, KEY_D1.7
unnamed: KEY_E1.2, KEY_E1.3
unnamed: KEY_E1.6, KEY_E1.7
unnamed: KEY_F1.2, KEY_F1.3
unnamed: KEY_F1.6, KEY_F1.7
unnamed: KEY_G1.2, KEY_G1.3
unnamed: KEY_G1.6, KEY_G1.7
unnamed: KEY_Q1.2, KEY_Q1.3
unnamed: KEY_Q1.6, KEY_Q1.7
unnamed: KEY_R1.2, KEY_R1.3
unnamed: KEY_R1.6, KEY_R1.7
unnamed: KEY_S1.2, KEY_S1.3
unnamed: KEY_S1.6, KEY_S1.7
unnamed: KEY_T1.2, KEY_T1.3
unnamed: KEY_T1.6, KEY_T1.7
unnamed: KEY_V1.2, KEY_V1.3
unnamed: KEY_V1.6, KEY_V1.7
unnamed: KEY_W1.2, KEY_W1.3
unnamed: KEY_W1.6, KEY_W1.7
unnamed: KEY_X1.2, KEY_X1.3
unnamed: KEY_X1.6, KEY_X1.7
unnamed: KEY_Z1.2, KEY_Z1.3
unnamed: KEY_Z1.6, KEY_Z1.7
unnamed: LEFT_ALT1.2, LEFT_ALT1.3
unnamed: LEFT_ALT1.6, LEFT_ALT1.7
unnamed: LEFT_CTRL1.2, LEFT_CTRL1.3
unnamed: LEFT_CTRL1.6, LEFT_CTRL1.7
unnamed: LEFT_HYPER1.2, LEFT_HYPER1.3
unnamed: LEFT_HYPER1.6, LEFT_HYPER1.7
unnamed: LEFT_SHIFT1.2, LEFT_SHIFT1.3
unnamed: LEFT_SHIFT1.6, LEFT_SHIFT1.7
unnamed: LEFT_SPACE1.2, LEFT_SPACE1.3
unnamed: LEFT_SPACE1.6, LEFT_SPACE1.7
unnamed: LEFT_WIN1.2, LEFT_WIN1.3
unnamed: LEFT_WIN1.6, LEFT_WIN1.7
unnamed: TAB1.2, TAB1.3
unnamed: TAB1.6, TAB1.7
unnamed: TILDE1.2, TILDE1.3
unnamed: TILDE1.6, TILDE1.7

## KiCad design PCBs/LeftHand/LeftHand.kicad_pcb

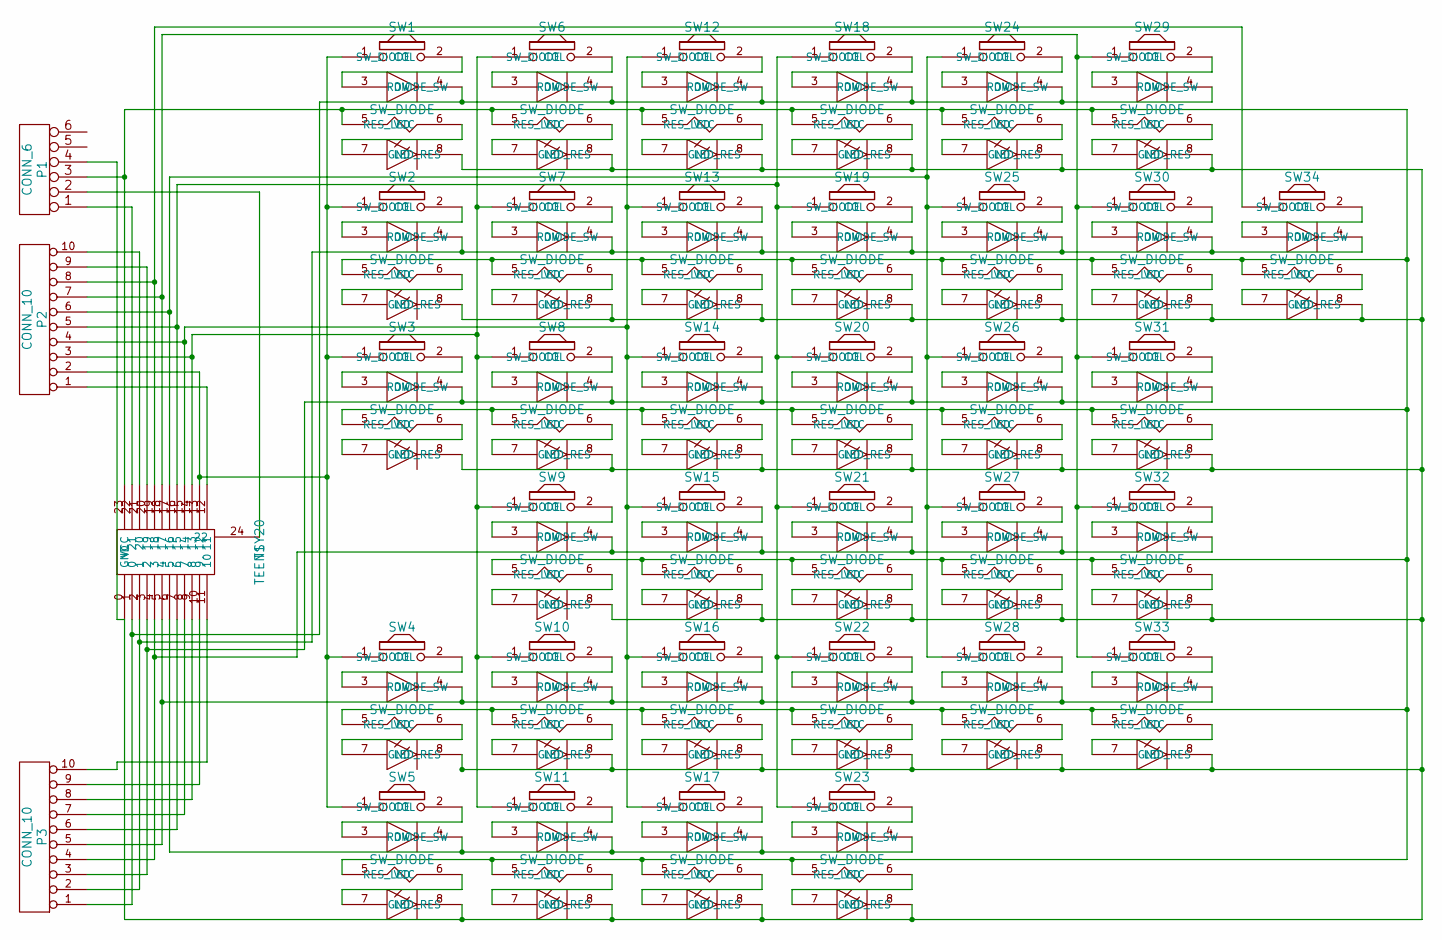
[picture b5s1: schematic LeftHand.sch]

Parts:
P1: CONN_6
P2, P3: CONN_10
SW1, SW2, SW3, SW4, SW5, SW6, SW7, SW8, SW9, SW10, SW11, SW12, SW13, SW14, SW15, SW16, SW17, SW18, SW19, SW20, SW21, SW22, SW23, SW24, SW25, SW26, SW27, SW28, SW29, SW30, SW31, SW32, SW33, SW34: SW_DIODE
T1: TEENSY20

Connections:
unnamed: P3.4, SW9.4 (ROW), SW15.4 (ROW), SW21.4 (ROW), SW27.4 (ROW), SW32.4 (ROW), T1.4 (3)
unnamed: SW5.4 (ROW), SW11.4 (ROW), SW17.4 (ROW), SW23.4 (ROW), T1.6 (5)
unnamed: P3.5, SW4.4 (ROW), SW10.4 (ROW), SW16.4 (ROW), SW22.4 (ROW), SW28.4 (ROW), SW33.4 (ROW), T1.5 (4)
unnamed: P1.4, SW1.8 (GND), SW2.8 (GND), SW3.8 (GND), SW4.8 (GND), SW5.8 (GND), SW6.8 (GND), SW7.8 (GND), SW8.8 (GND), SW9.8 (GND), SW10.8 (GND), SW11.8 (GND), SW12.8 (GND), SW13.8 (GND), SW14.8 (GND), SW15.8 (GND), SW16.8 (GND), SW17.8 (GND), SW18.8 (GND), SW19.8 (GND), SW20.8 (GND), SW21.8 (GND), SW22.8 (GND), SW23.8 (GND), SW24.8 (GND), SW25.8 (GND), SW26.8 (GND), SW27.8 (GND), SW28.8 (GND), SW29.8 (GND), SW30.8 (GND), SW31.8 (GND), SW32.8 (GND), SW33.8 (GND), SW34.8 (GND), T1.0 (GND)
unnamed: P3.3, SW3.4 (ROW), SW8.4 (ROW), SW14.4 (ROW), SW20.4 (ROW), SW26.4 (ROW), SW31.4 (ROW), T1.3 (2)
unnamed: SW11.6 (RES_LED), SW11.7 (LED_RES)
unnamed: SW5.2 (SW_DIODE), SW5.3 (DIODE_SW)
unnamed: SW5.6 (RES_LED), SW5.7 (LED_RES)
unnamed: SW10.2 (SW_DIODE), SW10.3 (DIODE_SW)
unnamed: SW10.6 (RES_LED), SW10.7 (LED_RES)
unnamed: SW11.2 (SW_DIODE), SW11.3 (DIODE_SW)
unnamed: SW16.2 (SW_DIODE), SW16.3 (DIODE_SW)
unnamed: SW16.6 (RES_LED), SW16.7 (LED_RES)
unnamed: SW17.2 (SW_DIODE), SW17.3 (DIODE_SW)
unnamed: SW17.6 (RES_LED), SW17.7 (LED_RES)
unnamed: SW30.6 (RES_LED), SW30.7 (LED_RES)
unnamed: SW31.2 (SW_DIODE), SW31.3 (DIODE_SW)
unnamed: SW31.6 (RES_LED), SW31.7 (LED_RES)
unnamed: SW32.2 (SW_DIODE), SW32.3 (DIODE_SW)
unnamed: SW32.6 (RES_LED), SW32.7 (LED_RES)
unnamed: SW34.2 (SW_DIODE), SW34.3 (DIODE_SW)
unnamed: SW34.6 (RES_LED), SW34.7 (LED_RES)
unnamed: SW4.2 (SW_DIODE), SW4.3 (DIODE_SW)
unnamed: SW4.6 (RES_LED), SW4.7 (LED_RES)
unnamed: SW28.2 (SW_DIODE), SW28.3 (DIODE_SW)
unnamed: SW22.2 (SW_DIODE), SW22.3 (DIODE_SW)
unnamed: SW22.6 (RES_LED), SW22.7 (LED_RES)
unnamed: SW23.2 (SW_DIODE), SW23.3 (DIODE_SW)
unnamed: SW23.6 (RES_LED), SW23.7 (LED_RES)
unnamed: SW28.6 (RES_LED), SW28.7 (LED_RES)
unnamed: SW33.2 (SW_DIODE), SW33.3 (DIODE_SW)
unnamed: SW33.6 (RES_LED), SW33.7 (LED_RES)
unnamed: P2.8, SW34.1 (COL), T1.19 (18)
unnamed: P2.10, T1.21 (20)
unnamed: P2.9, T1.20 (19)
unnamed: P1.1, T1.22 (21)
unnamed: P1.2, T1.24 (22)
unnamed: P3.7, T1.8 (7)
unnamed: P3.6, T1.7 (6)
unnamed: P3.8, T1.9 (8)
unnamed: P3.9, T1.10 (9)
unnamed: P3.10, T1.11 (10)
unnamed: P2.1, T1.12 (11)
unnamed: P3.1, SW1.4 (ROW), SW6.4 (ROW), SW12.4 (ROW), SW18.4 (ROW), SW24.4 (ROW), SW29.4 (ROW), T1.1 (0)
unnamed: P2.7, SW29.1 (COL), SW30.1 (COL), SW31.1 (COL), SW32.1 (COL), SW33.1 (COL), T1.18 (17)
unnamed: P3.2, SW2.4 (ROW), SW7.4 (ROW), SW13.4 (ROW), SW19.4 (ROW), SW25.4 (ROW), SW30.4 (ROW), SW34.4 (ROW), T1.2 (1)
unnamed: P2.6, SW24.1 (COL), SW25.1 (COL), SW26.1 (COL), SW27.1 (COL), SW28.1 (COL), T1.17 (16)
unnamed: P1.3, SW1.5 (VCC), SW2.5 (VCC), SW3.5 (VCC), SW4.5 (VCC), SW5.5 (VCC), SW6.5 (VCC), SW7.5 (VCC), SW8.5 (VCC), SW9.5 (VCC), SW10.5 (VCC), SW11.5 (VCC), SW12.5 (VCC), SW13.5 (VCC), SW14.5 (VCC), SW15.5 (VCC), SW16.5 (VCC), SW17.5 (VCC), SW18.5 (VCC), SW19.5 (VCC), SW20.5 (VCC), SW21.5 (VCC), SW22.5 (VCC), SW23.5 (VCC), SW24.5 (VCC), SW25.5 (VCC), SW26.5 (VCC), SW27.5 (VCC), SW28.5 (VCC), SW29.5 (VCC), SW30.5 (VCC), SW31.5 (VCC), SW32.5 (VCC), SW33.5 (VCC), SW34.5 (VCC), T1.23 (VCC)
unnamed: P2.3, SW6.1 (COL), SW7.1 (COL), SW8.1 (COL), SW9.1 (COL), SW10.1 (COL), SW11.1 (COL), T1.14 (13)
unnamed: P2.2, SW1.1 (COL), SW2.1 (COL), SW3.1 (COL), SW4.1 (COL), SW5.1 (COL), T1.13 (12)
unnamed: P2.5, SW18.1 (COL), SW19.1 (COL), SW20.1 (COL), SW21.1 (COL), SW22.1 (COL), SW23.1 (COL), T1.16 (15)
unnamed: P2.4, SW12.1 (COL), SW13.1 (COL), SW14.1 (COL), SW15.1 (COL), SW16.1 (COL), SW17.1 (COL), T1.15 (14)
unnamed: SW20.2 (SW_DIODE), SW20.3 (DIODE_SW)
unnamed: SW18.6 (RES_LED), SW18.7 (LED_RES)
unnamed: SW19.2 (SW_DIODE), SW19.3 (DIODE_SW)
unnamed: SW19.6 (RES_LED), SW19.7 (LED_RES)
unnamed: SW20.6 (RES_LED), SW20.7 (LED_RES)
unnamed: SW21.2 (SW_DIODE), SW21.3 (DIODE_SW)
unnamed: SW21.6 (RES_LED), SW21.7 (LED_RES)
unnamed: SW15.2 (SW_DIODE), SW15.3 (DIODE_SW)
unnamed: SW15.6 (RES_LED), SW15.7 (LED_RES)
unnamed: SW18.2 (SW_DIODE), SW18.3 (DIODE_SW)
unnamed: SW25.6 (RES_LED), SW25.7 (LED_RES)
unnamed: SW26.2 (SW_DIODE), SW26.3 (DIODE_SW)
unnamed: SW26.6 (RES_LED), SW26.7 (LED_RES)
unnamed: SW27.6 (RES_LED), SW27.7 (LED_RES)
unnamed: SW24.2 (SW_DIODE), SW24.3 (DIODE_SW)
unnamed: SW24.6 (RES_LED), SW24.7 (LED_RES)
unnamed: SW25.2 (SW_DIODE), SW25.3 (DIODE_SW)
unnamed: SW6.2 (SW_DIODE), SW6.3 (DIODE_SW)
unnamed: SW6.6 (RES_LED), SW6.7 (LED_RES)
unnamed: SW7.6 (RES_LED), SW7.7 (LED_RES)
unnamed: SW1.2 (SW_DIODE), SW1.3 (DIODE_SW)
unnamed: SW1.6 (RES_LED), SW1.7 (LED_RES)
unnamed: SW2.2 (SW_DIODE), SW2.3 (DIODE_SW)
unnamed: SW2.6 (RES_LED), SW2.7 (LED_RES)
unnamed: SW3.2 (SW_DIODE), SW3.3 (DIODE_SW)
unnamed: SW3.6 (RES_LED), SW3.7 (LED_RES)
unnamed: SW13.2 (SW_DIODE), SW13.3 (DIODE_SW)
unnamed: SW12.2 (SW_DIODE), SW12.3 (DIODE_SW)
unnamed: SW12.6 (RES_LED), SW12.7 (LED_RES)
unnamed: SW13.6 (RES_LED), SW13.7 (LED_RES)
unnamed: SW14.2 (SW_DIODE), SW14.3 (DIODE_SW)
unnamed: SW14.6 (RES_LED), SW14.7 (LED_RES)
unnamed: SW8.2 (SW_DIODE), SW8.3 (DIODE_SW)
unnamed: SW8.6 (RES_LED), SW8.7 (LED_RES)
unnamed: SW9.2 (SW_DIODE), SW9.3 (DIODE_SW)
unnamed: SW9.6 (RES_LED), SW9.7 (LED_RES)
unnamed: SW7.2 (SW_DIODE), SW7.3 (DIODE_SW)
unnamed: SW27.2 (SW_DIODE), SW27.3 (DIODE_SW)
unnamed: SW29.2 (SW_DIODE), SW29.3 (DIODE_SW)
unnamed: SW29.6 (RES_LED), SW29.7 (LED_RES)
unnamed: SW30.2 (SW_DIODE), SW30.3 (DIODE_SW)

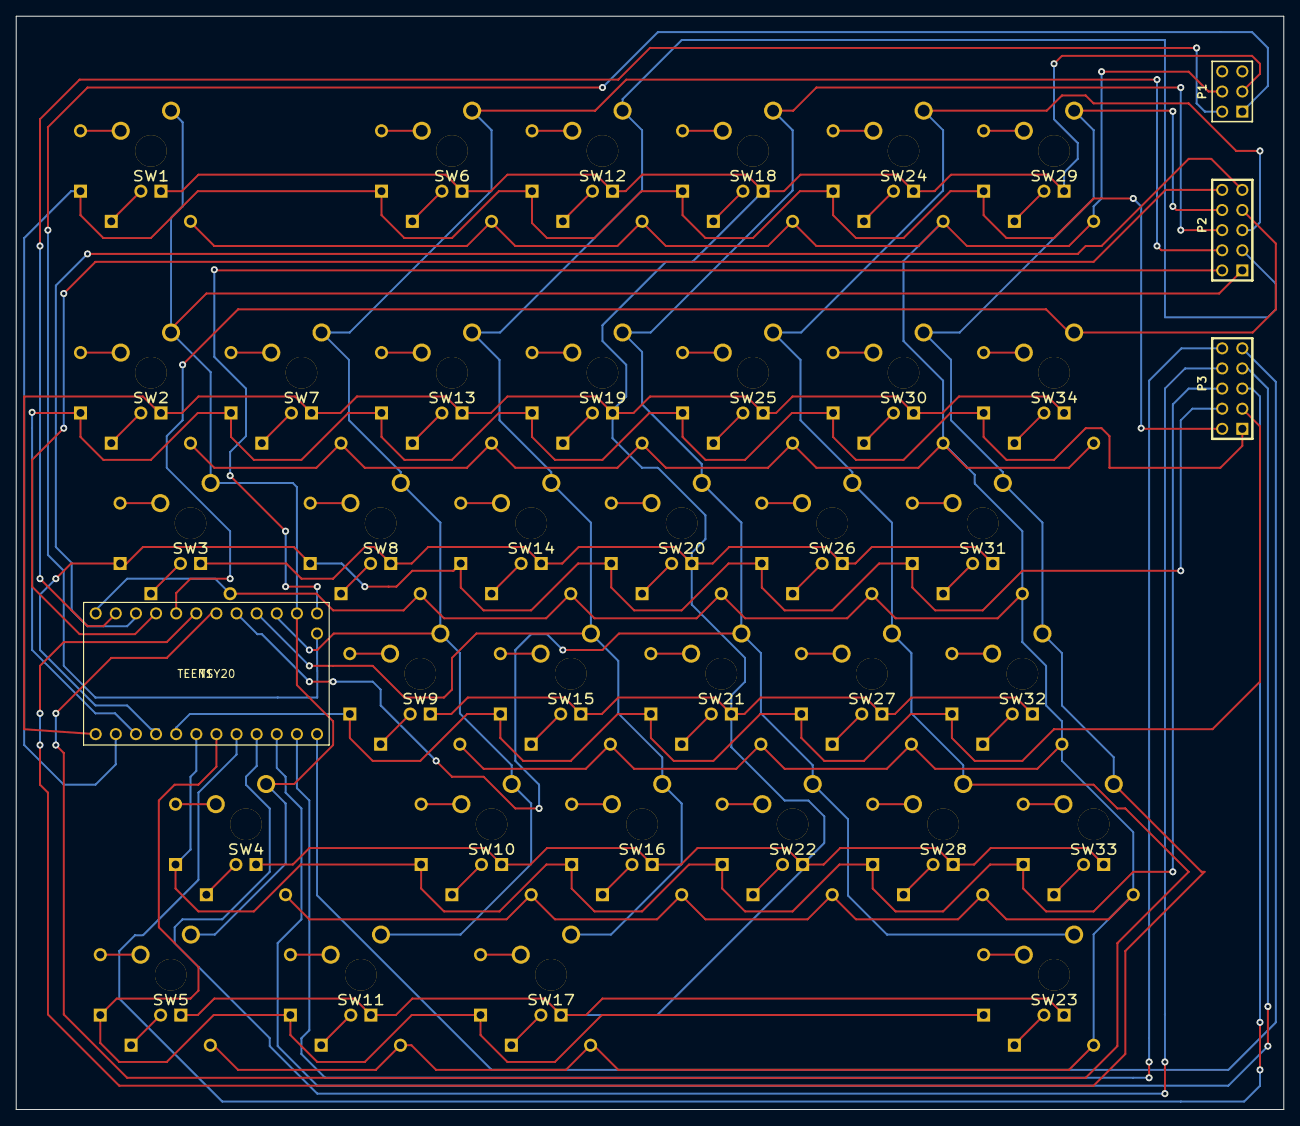
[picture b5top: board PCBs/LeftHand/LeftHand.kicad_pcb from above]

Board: 2 copper layers, 160.0 x 138.0 mm, 38 parts (0 on the bottom side), 93 nets.
